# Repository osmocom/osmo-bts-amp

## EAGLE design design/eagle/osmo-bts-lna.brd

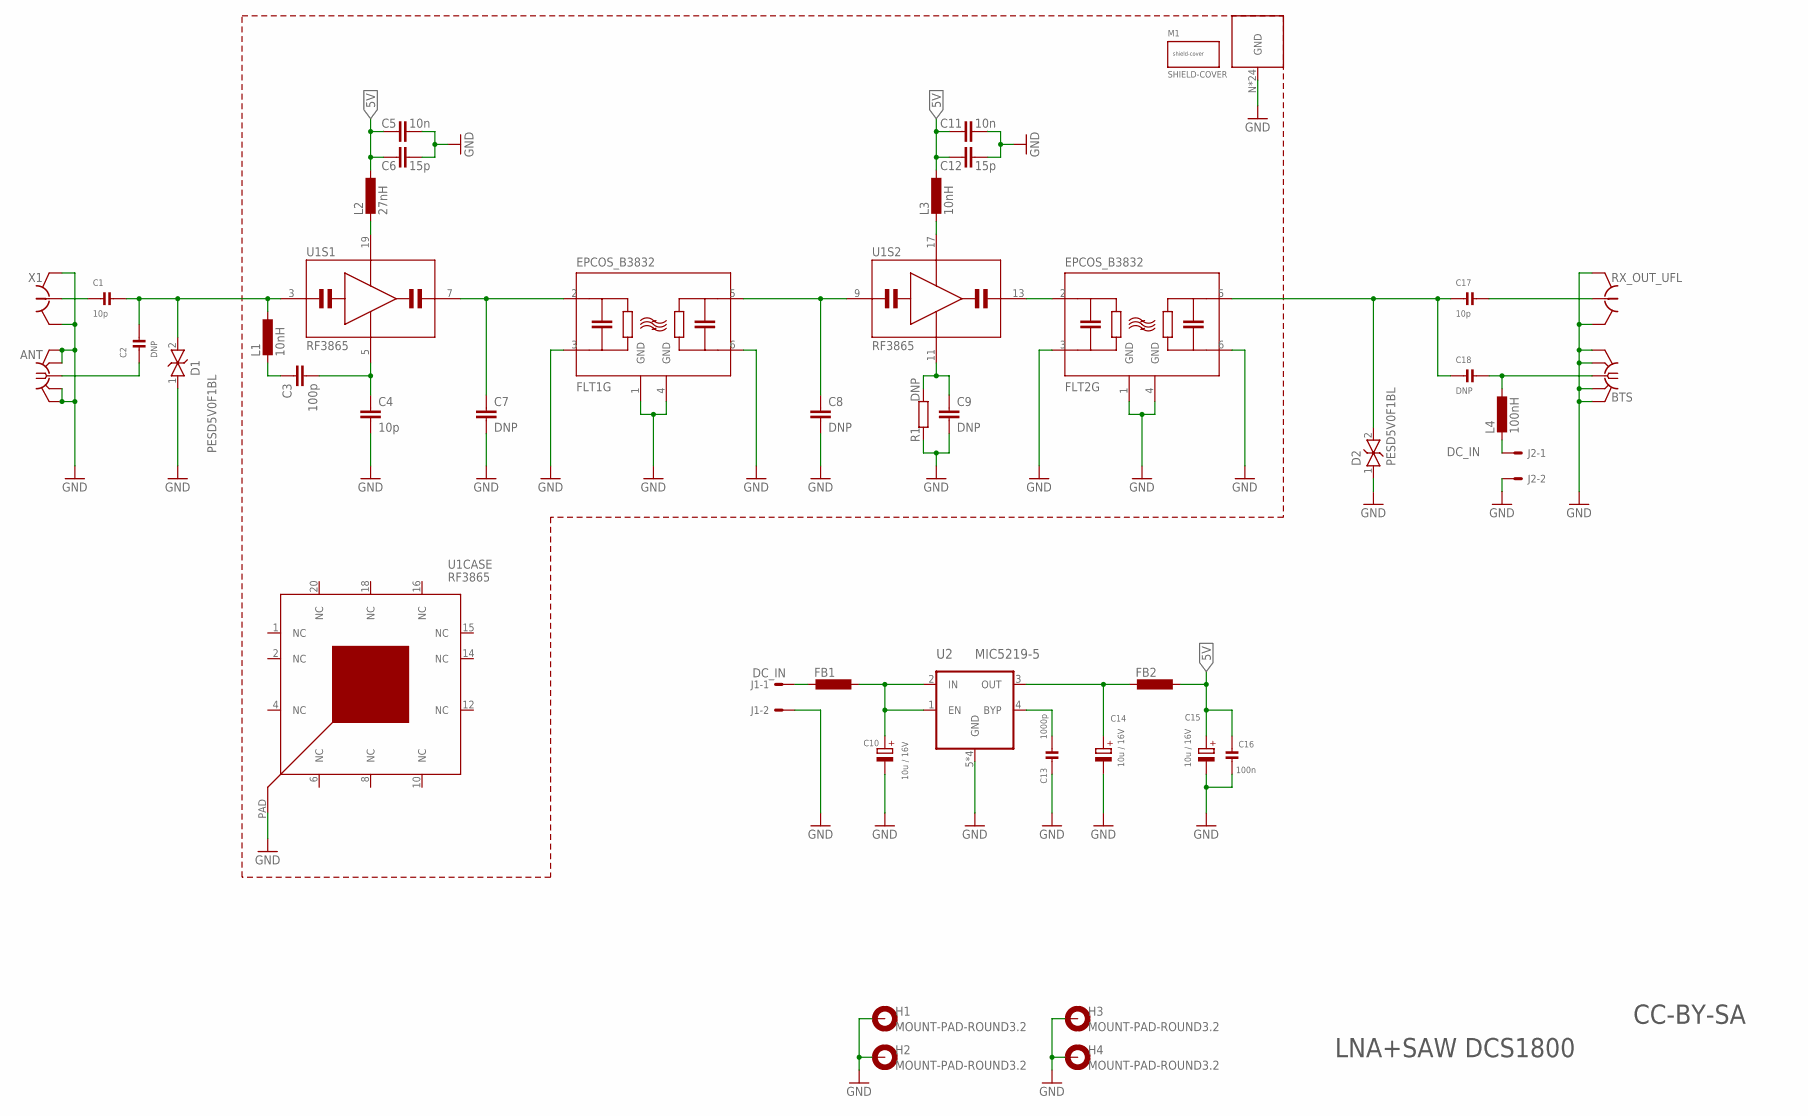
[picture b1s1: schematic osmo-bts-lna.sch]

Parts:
ANT: SMA-F-S-EDGE; MANUFACTURERPARTNUMBER UNKNOWN MANUFACTURER PART NUMBER
BTS: SMA-F-S-EDGE; MANUFACTURERPARTNUMBER UNKNOWN MANUFACTURER PART NUMBER
C1, C17: 10p; _0603; MANUFACTURERPARTNUMBER C0603C100J5GACTU
C2, C18: DNP; _0603; MANUFACTURERPARTNUMBER UNKNOWN MANUFACTURER PART NUMBER
C3: 100p; 0603; MANUFACTURERPARTNUMBER 06035A101FAT2A
C4: 10p; 0603; MANUFACTURERPARTNUMBER C0603C100J5GACTU
C5, C11: 10n; 0603; MANUFACTURERPARTNUMBER GCM188R72A103KA37D
C6, C12: 15p; 0603; MANUFACTURERPARTNUMBER CL10C150JB8NCNC
C7, C8, C9: DNP; 0603; MANUFACTURERPARTNUMBER UNKNOWN MANUFACTURER PART NUMBER
C10, C14, C15: 10u / 16V; CPOL1206; MANUFACTURERPARTNUMBER CL21A106KOCLRNC
C13: 1000p; _0603; MANUFACTURERPARTNUMBER CC0402KRX7R7BB102
C16: 100n; _0603; MANUFACTURERPARTNUMBER CL10B104KO8NNNC
D1, D2: PESD5V0F1BL; SOD882; MANUFACTURERPARTNUMBER PESD5V0F1BL,315
FB1: FBEAD_1206; 1206; MANUFACTURERPARTNUMBER HZ0805D102R-10
FB2: INDUCTOR0603; 0603; MANUFACTURERPARTNUMBER HZ0805D102R-10
FLT1, FLT2: EPCOS_B3832; DCC6C; MANUFACTURERPARTNUMBER UNKNOWN MANUFACTURER PART NUMBER
H1, H2, H3, H4: MOUNT-PAD-ROUND3.2; 3,2-PAD; MANUFACTURERPARTNUMBER UNKNOWN MANUFACTURER PART NUMBER
J1, J2: DC_IN; 6410-02; MANUFACTURERPARTNUMBER UNKNOWN MANUFACTURER PART NUMBER
L1, L3: 10nH; 0603; MANUFACTURERPARTNUMBER PM0603-10NJ-RC
L2: 27nH; 0603; MANUFACTURERPARTNUMBER PM0603-27NJ-RC
L4: 100nH; _0402; MANUFACTURERPARTNUMBER LQG15HHR10J02D
R1: DNP; 0603; MANUFACTURERPARTNUMBER UNKNOWN MANUFACTURER PART NUMBER
RX_OUT_UFL: HRS_UFL; MANUFACTURERPARTNUMBER U.FL-R-SMT(01)
SHLD1: SHIELD-BMI-S-204; BMI-S-204; MANUFACTURERPARTNUMBER BMI-S-204-F
U1: RF3865; QFN20_5X5_PAD; MANUFACTURERPARTNUMBER UNKNOWN MANUFACTURER PART NUMBER
U2: MIC5219-5; MSOP8; MANUFACTURERPARTNUMBER MIC5219-5.0YMM
X1: HRS_UFL; MANUFACTURERPARTNUMBER U.FL-R-SMT(01)

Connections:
5V: C5.1, C6.1, C11.1, C12.1, C15.+, C16.1, FB2.2, L2.1, L3.1
DC_IN: FB1.1, J1.1
DC_IN_FLT: C10.+, FB1.2, U2.1 (EN), U2.2 (IN)
GND: ANT.BG1 (GND), ANT.BG2 (GND), ANT.TG1 (GND), ANT.TG2 (GND), BTS.BG1 (GND), BTS.BG2 (GND), BTS.TG1 (GND), BTS.TG2 (GND), C4.2, C5.2, C6.2, C7.2, C8.2, C9.2, C10.-, C11.2, C12.2, C13.2, C14.-, C15.-, C16.2, D1.1, D2.1, FLT1.1 (GND), FLT1.3 (IN_GND), FLT1.4 (GND), FLT1.6 (OUT_GND), FLT2.1 (GND), FLT2.3 (IN_GND), FLT2.4 (GND), FLT2.6 (OUT_GND), H1.B3,2, H2.B3,2, H3.B3,2, H4.B3,2, J1.2, J2.2, R1.1, RX_OUT_UFL.GND@1 (GND), RX_OUT_UFL.GND@2 (GND), SHLD1.N, SHLD1.NNE, SHLD1.NNE1, SHLD1.NNE2, SHLD1.NNE4, SHLD1.NNE5, SHLD1.NNW, SHLD1.S, SHLD1.S1, SHLD1.S2, SHLD1.S3, SHLD1.S4, SHLD1.S5, SHLD1.S6, SHLD1.S7, SHLD1.S8, SHLD1.S9, SHLD1.SSE, SHLD1.SSW, SHLD1.SSW1, SHLD1.SSW2, SHLD1.SSW3, SHLD1.SSW4, SHLD1.SSW5, U1.PAD (CASE_GND), U2.5 (GND), U2.6 (GND), U2.7 (GND), U2.8 (GND), X1.GND@1 (GND), X1.GND@2 (GND)
unnamed: L2.2, U1.19 (VDD)
unnamed: ANT.C (1), C2.1
unnamed: C13.1, U2.4 (BYP)
unnamed: C3.1, L1.2
unnamed: C3.2, C4.1, U1.5 (AC_GND)
unnamed: C9.1, R1.2, U1.11 (AC_GND)
unnamed: C1.1, X1.SIG (1)
unnamed: C17.2, RX_OUT_UFL.SIG (1)
unnamed: C17.1, C18.1, D2.2, FLT2.5 (OUT)
unnamed: L3.2, U1.17 (VDD)
unnamed: J2.1, L4.2
unnamed: C14.+, FB2.1, U2.3 (OUT)
RF_UPLINK: C1.2, C2.2, D1.2, L1.1, U1.3 (RF_IN)
RF_UPLINK_IS_IN: C8.1, FLT1.5 (OUT), U1.9 (RF_IN)
RF_UPLINK_IS_OUT: C7.1, FLT1.2 (IN), U1.7 (RF_OUT)
RF_UPLINK_LNA_OUT: FLT2.2 (IN), U1.13 (RF_OUT)
RF_UPLINK_OUT: BTS.C (1), C18.2, L4.1

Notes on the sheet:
LNA+SAW DCS1800
CC-BY-SA

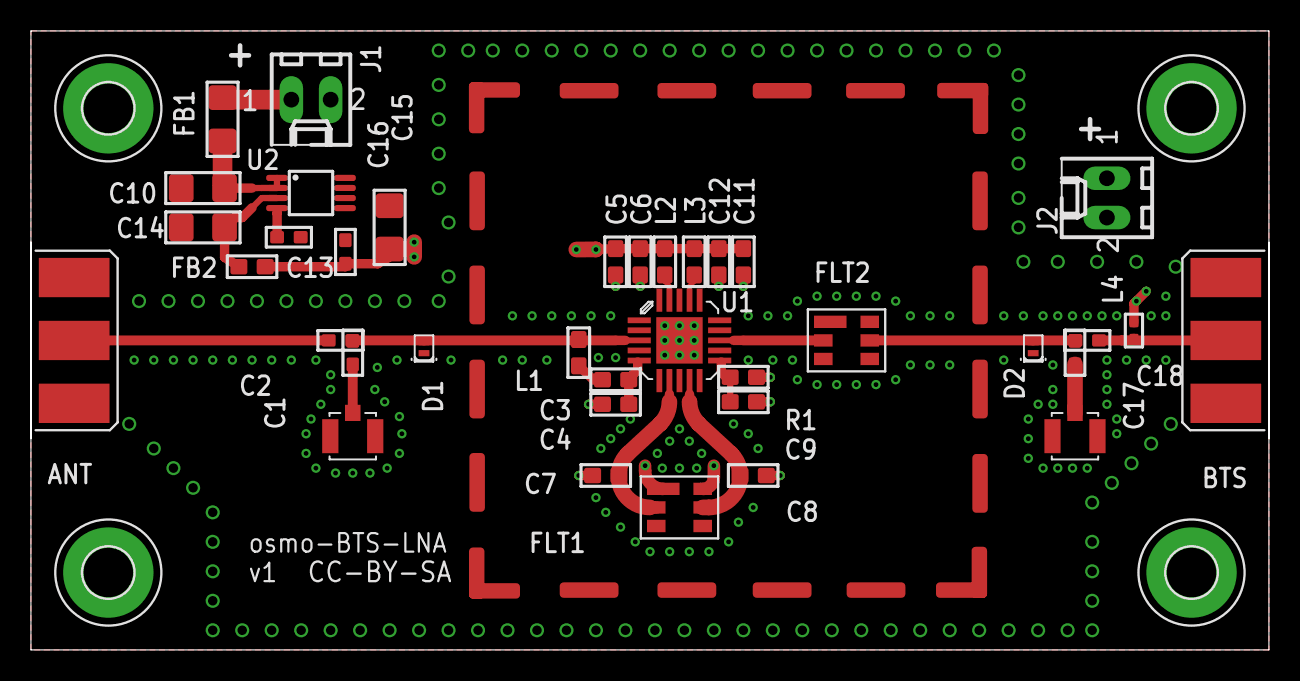
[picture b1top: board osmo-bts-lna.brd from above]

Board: 4 copper layers, 80.0 x 40.0 mm, 42 parts (0 on the bottom side), 21 nets.

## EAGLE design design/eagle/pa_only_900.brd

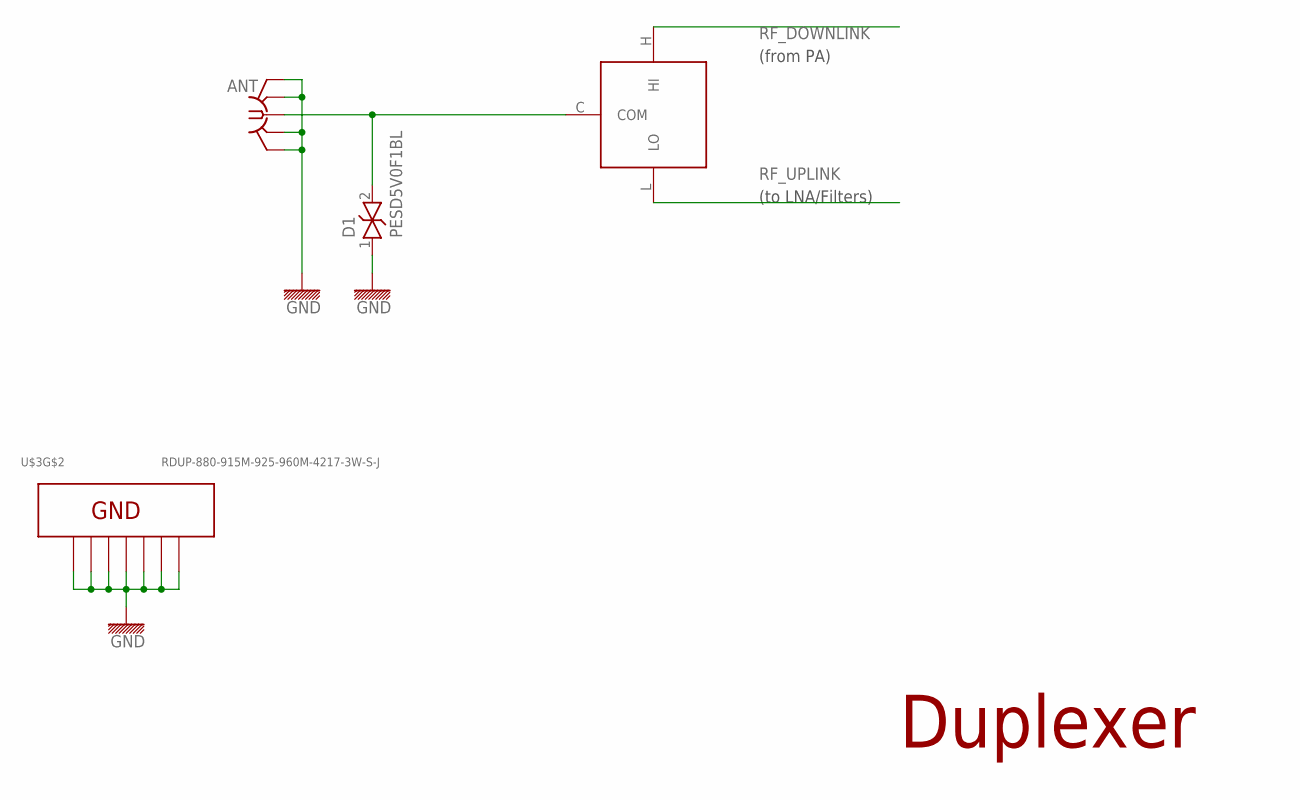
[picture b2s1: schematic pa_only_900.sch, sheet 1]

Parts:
ANT: SMA-F-S-TH
D1: PESD5V0F1BL; SOD882
U$3: RDUP-880-915M-925-960M-4217-3W-S-J; RADITEK_4217

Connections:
GND: ANT.G1 (GND), ANT.G2 (GND), ANT.G3 (GND), ANT.G4 (GND), D1.1, U$3.G1, U$3.G2, U$3.G3, U$3.G4, U$3.G5, U$3.G6, U$3.G7; also elsewhere on the board
RF_ANT: ANT.C (1), D1.2, U$3.C (COM)
RF_DOWNLINK: U$3.H (HI); also elsewhere on the board
RF_UPLINK: U$3.L (LO); also elsewhere on the board

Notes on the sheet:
(from PA)
(to LNA/Filters)
Duplexer

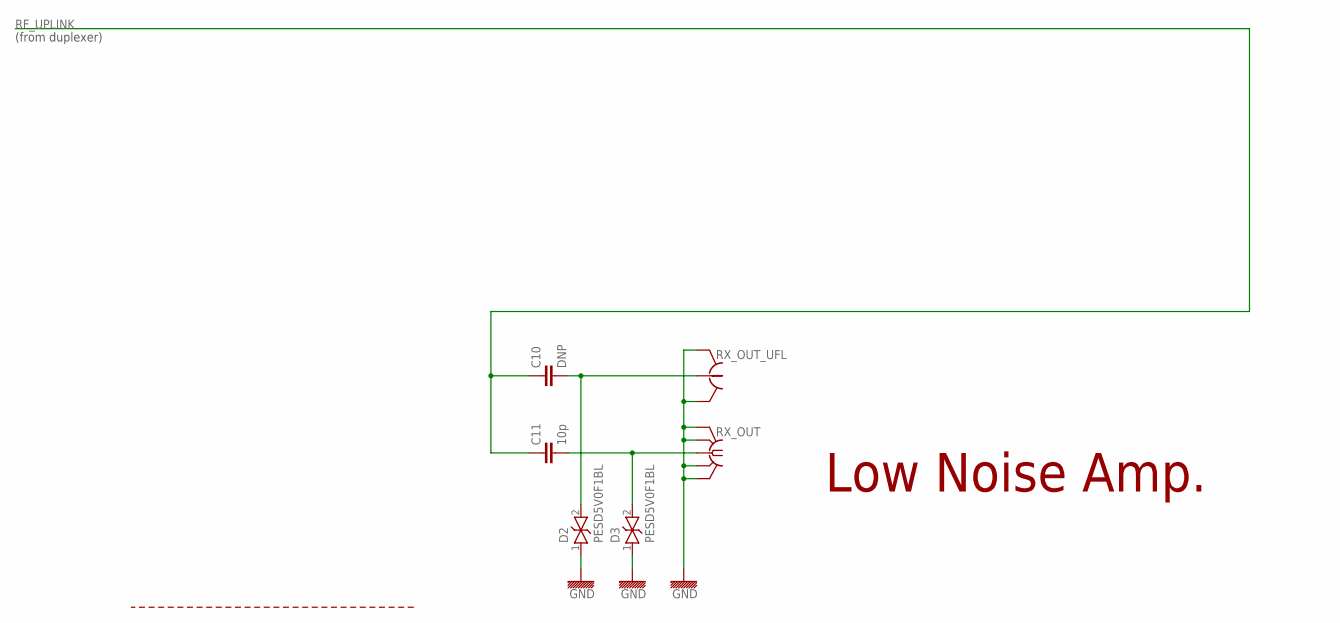
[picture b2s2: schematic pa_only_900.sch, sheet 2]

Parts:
C10: DNP; 0603
C11: 10p; 0603
D2, D3: PESD5V0F1BL; SOD882
RX_OUT: SMA-F-S-TH
RX_OUT_UFL: HRS_UFL

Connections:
GND: D2.1, D3.1, RX_OUT.G1 (GND), RX_OUT.G2 (GND), RX_OUT.G3 (GND), RX_OUT.G4 (GND), RX_OUT_UFL.GND@1 (GND), RX_OUT_UFL.GND@2 (GND); also elsewhere on the board
unnamed: C10.2, D2.2, RX_OUT_UFL.SIG (1)
RF_UPLINK: C10.1, C11.1; also elsewhere on the board
RF_UPLINK_OUT: C11.2, D3.2, RX_OUT.C (1)

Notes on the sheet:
(from duplexer)
Low Noise Amp.

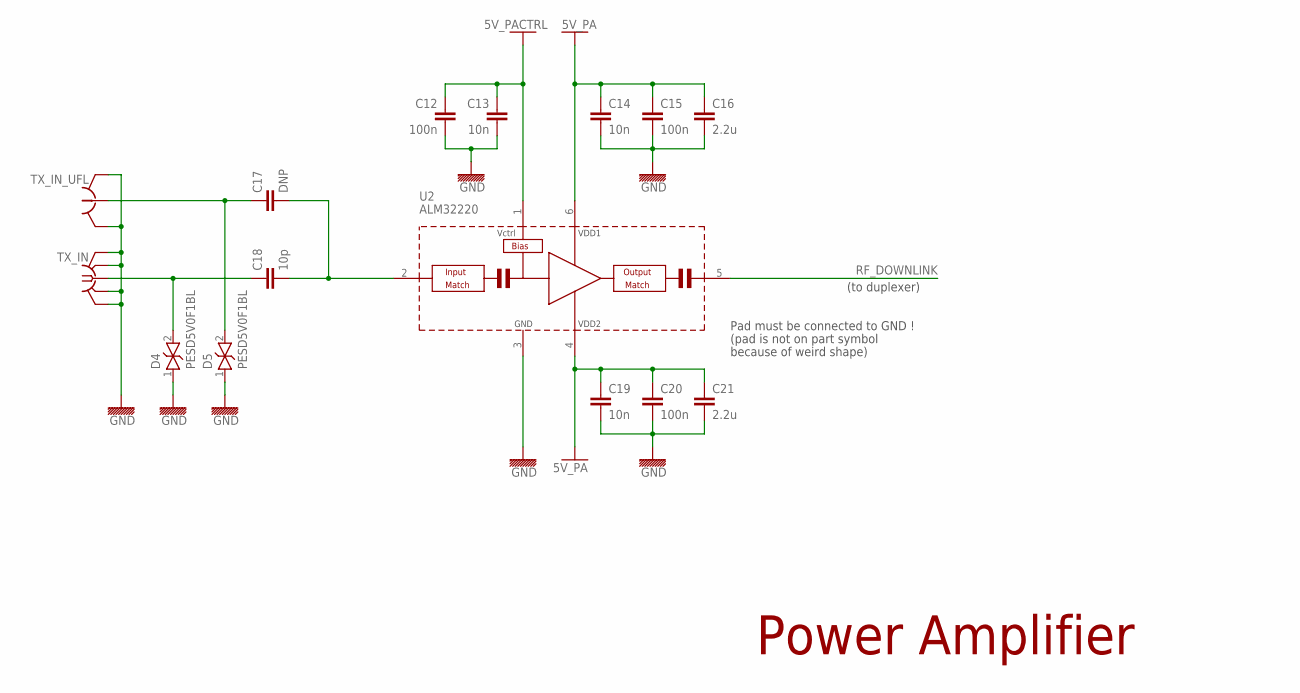
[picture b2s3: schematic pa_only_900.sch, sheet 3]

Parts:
C12, C15, C20: 100n; 0603
C13, C14, C19: 10n; 0603
C16, C21: 2.2u; 0805
C17: DNP; 0603
C18: 10p; 0603
D4, D5: PESD5V0F1BL; SOD882
TX_IN: SMA-F-S-TH
TX_IN_UFL: HRS_UFL
U2: ALM32220; ALM32X20

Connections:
5V_PA: C14.1, C15.1, C16.1, C19.1, C20.1, C21.1, U2.4 (VDD2), U2.6 (VDD1); also elsewhere on the board
5V_PACTRL: C12.1, C13.1, U2.1 (VCTRL); also elsewhere on the board
GND: C12.2, C13.2, C14.2, C15.2, C16.2, C19.2, C20.2, C21.2, D4.1, D5.1, TX_IN.G1 (GND), TX_IN.G2 (GND), TX_IN.G3 (GND), TX_IN.G4 (GND), TX_IN_UFL.GND@1 (GND), TX_IN_UFL.GND@2 (GND), U2.3 (GND); also elsewhere on the board
unnamed: C18.1, D4.2, TX_IN.C (1)
unnamed: C17.2, C18.2, U2.2 (RF_IN)
unnamed: C17.1, D5.2, TX_IN_UFL.SIG (1)
RF_DOWNLINK: U2.5 (RF_OUT); also elsewhere on the board

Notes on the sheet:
(to duplexer)
Pad must be connected to GND !
(pad is not on part symbol
because of weird shape)
Power Amplifier

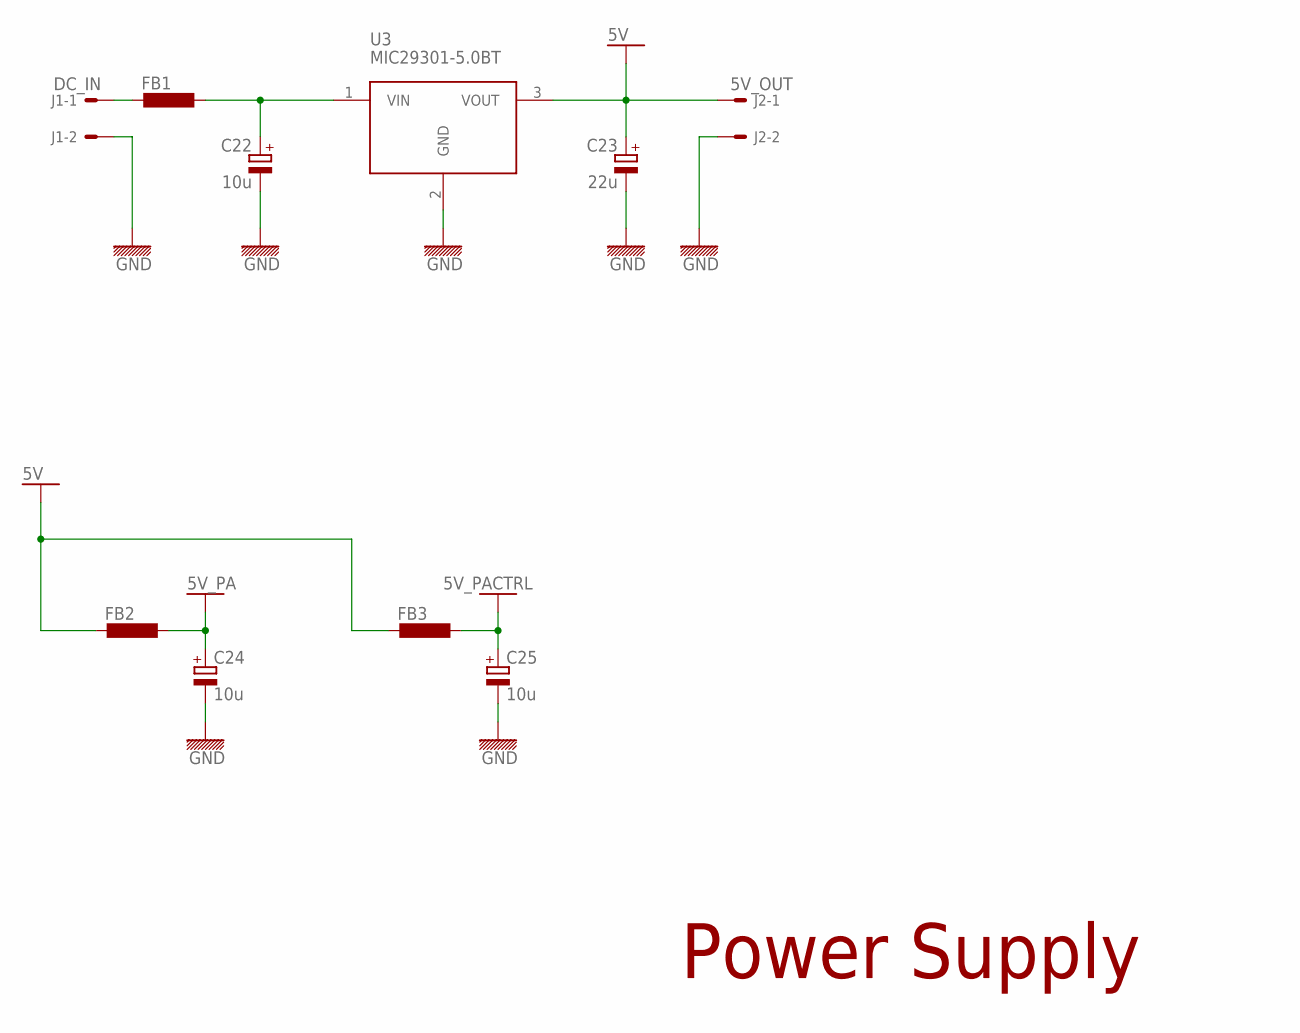
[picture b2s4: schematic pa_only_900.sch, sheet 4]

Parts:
C22, C24, C25: 10u; SMC_A
C23: 22u; SMC_A
FB1, FB2: FBEAD_1206; 1206
FB3: FBEAD_0603; 0603
J1: DC_IN; 6410-02
J2: 5V_OUT; 6410-02
U3: MIC29301-5.0BT; TO220BV

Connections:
5V: C23.+, FB2.1, FB3.1, J2.1, U3.3 (VOUT)
5V_PA: C24.+, FB2.2; also elsewhere on the board
5V_PACTRL: C25.+, FB3.2; also elsewhere on the board
DC_IN: FB1.1, J1.1
DC_IN_FLT: C22.+, FB1.2, U3.1 (VIN)
GND: C22.-, C23.-, C24.-, C25.-, J1.2, J2.2, U3.2 (GND); also elsewhere on the board

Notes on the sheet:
Power Supply

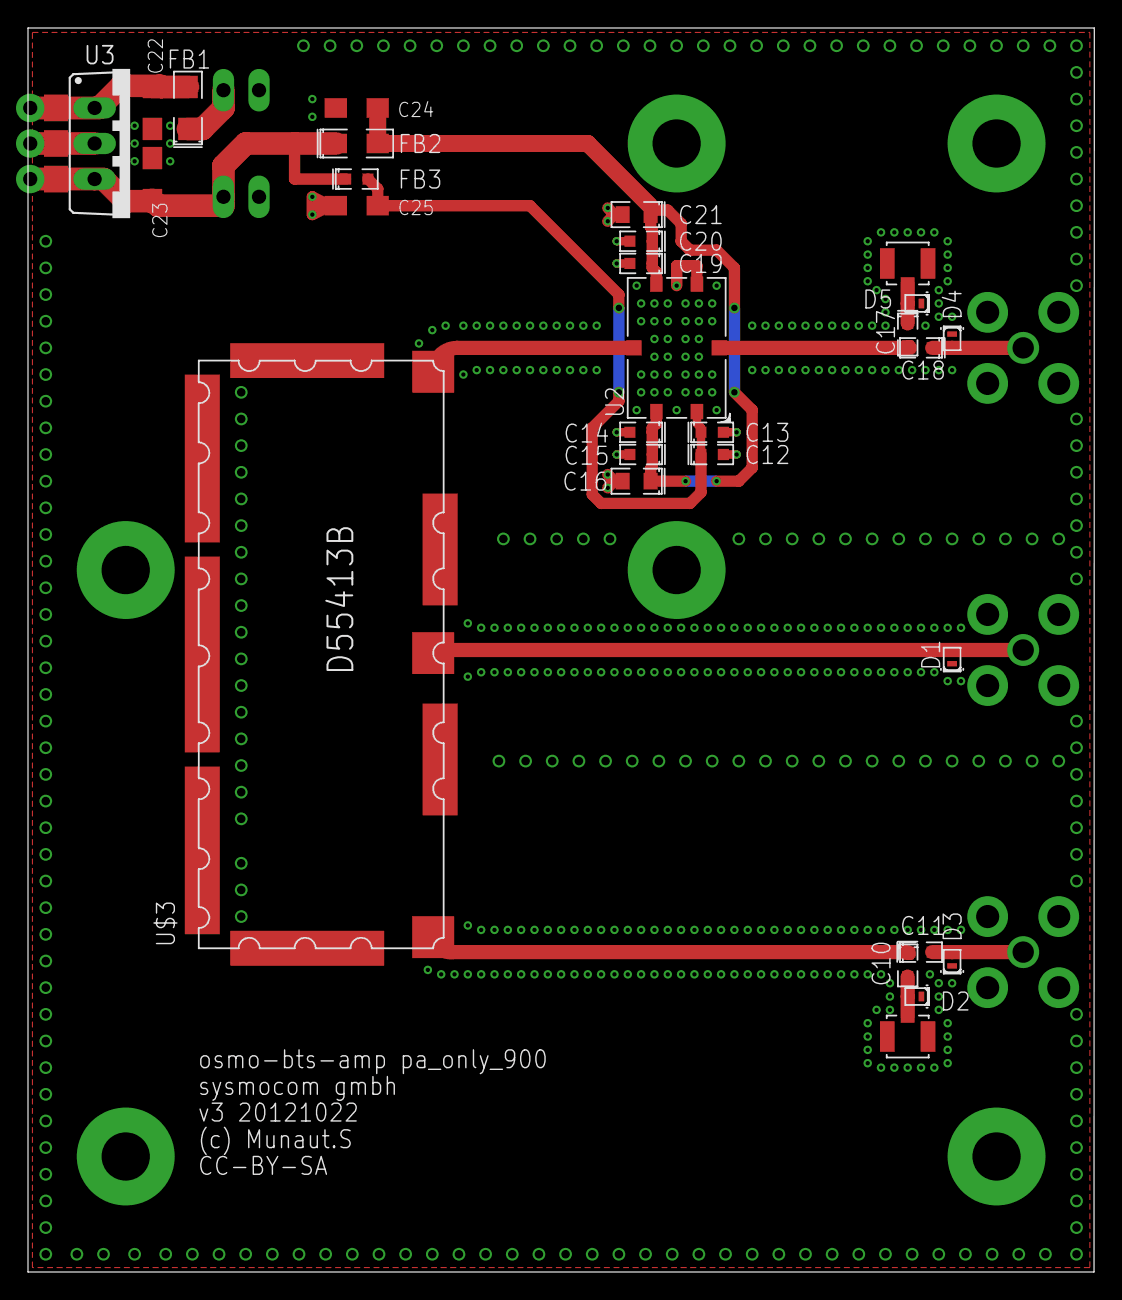
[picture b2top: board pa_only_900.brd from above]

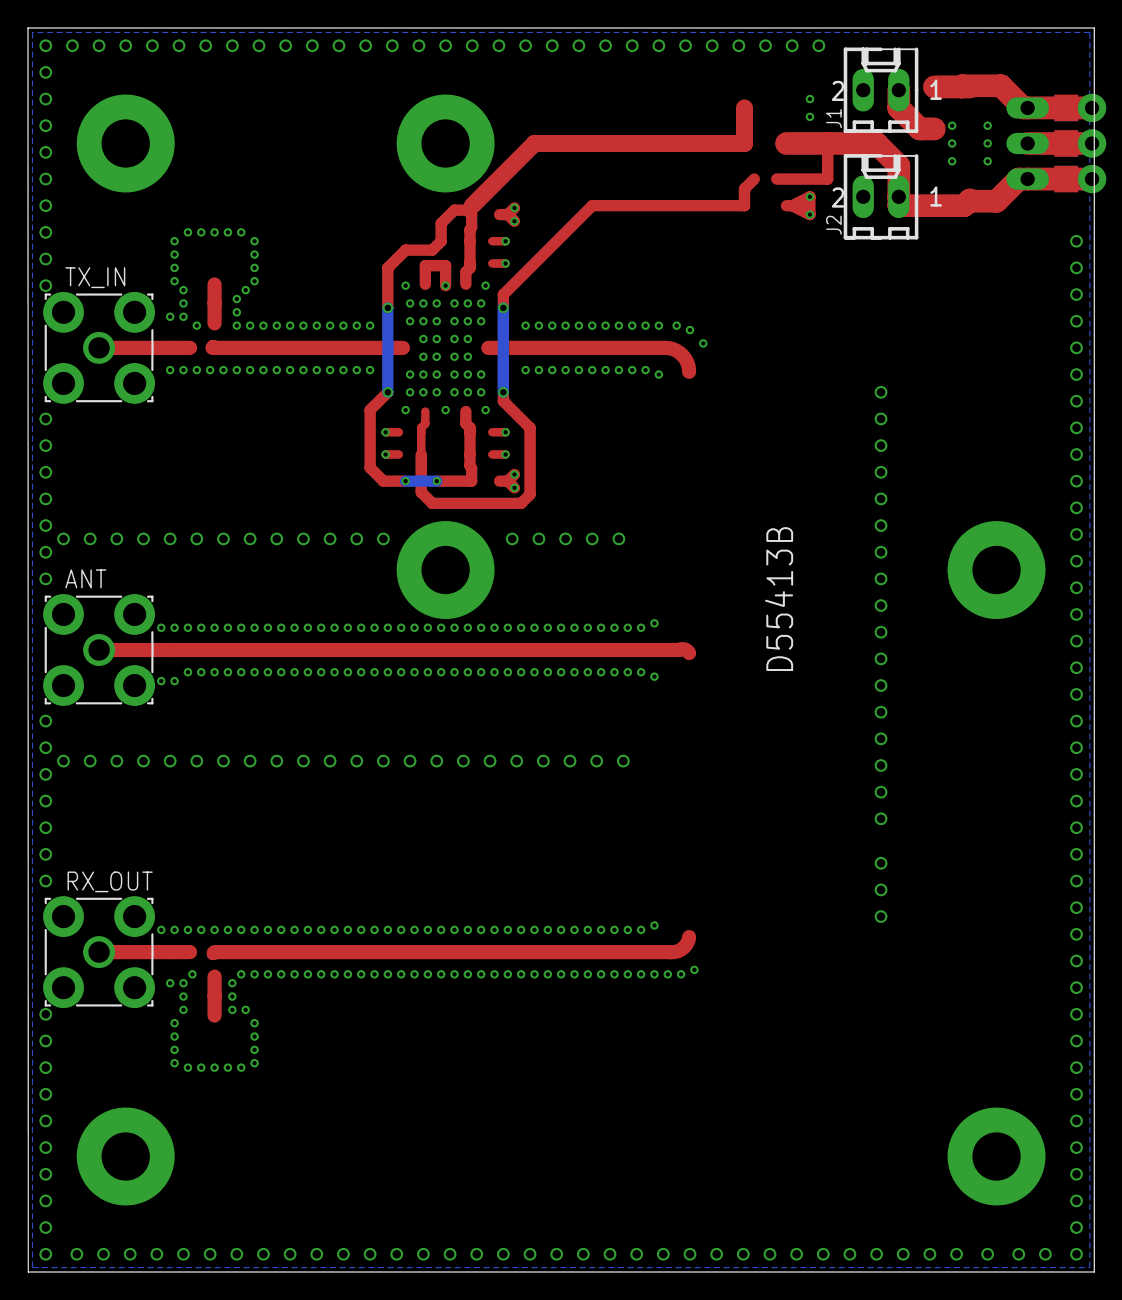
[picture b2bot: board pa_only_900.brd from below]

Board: 2 copper layers, 76.2 x 88.9 mm, 34 parts (5 on the bottom side), 14 nets.

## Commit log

2012-01-11 initial import of mini-amp project
2012-01-11 add more data sheets
2012-01-11 add datasheet of epcos filter
2012-05-17 add fischer case drawing
2012-05-18 design: Add gitignore for eagle backup files
2012-05-18 design: Remove sch & brd because they were binaries from Eagle v5.x
2012-05-18 design: Import original design as Eagle 6.x XML format
    This is pretty much the first manufactured board. (just a couple
    of solder mask fixes)
2012-05-18 design: Major revision of the PCB to fit into enclosure
2012-05-18 design: Move the outside holes closer to their optimal position
    According to the WAG100 datasheet they should be 36.25 mm from the center
    axis. Now they are 36.2 mm from the center axis which should work fine.
2012-05-19 design: Make the traces 40 mil wide with 12 mil GND separaton
    This should keep a ~ 55 ohm impedance (close enough)
2012-05-19 import partlist and BOM
2012-05-21 BOM: use 25x25 mm shielding cover, not 30x30
    The BOM contained the wrong part numbers for the shielding cover
2012-09-20 add more recent schematics + gerber renderings
2012-10-22 move dimensions a bit closer to the PCB for print view
    (allows larger scaling on A4 printout)
2012-10-22 for pa_only_1800 as copy of frontend_v2
2012-10-22 add a PA-only version without LNA for DCS 1800
2012-10-22 Start a PA-only version for GSM 900
2012-10-22 schematics / gerber of 900 MHz PA-only version
2012-10-22 update data sheets, add some GSM900 variants
2014-06-30 add current ALM data sheets and application note
2018-04-10 BTS-LNA: add eBOM for 1st production run
2019-01-15 bts-lna: add/update design files, add schema + PCB as pdf
